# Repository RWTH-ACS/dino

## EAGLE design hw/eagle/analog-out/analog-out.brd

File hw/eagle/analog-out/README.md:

dino analog-out
Copyright (c) 2022 Manuel Pitz
Copyright (c) 2022 Niklas Eiling

This repository describes Open Hardware and is licensed under the CERN-OHL-W v2

You may redistribute and modify this documentation and make products
using it under the terms of the CERN-OHL-W v2 (https:/cern.ch/cern-ohl).
This documentation is distributed WITHOUT ANY EXPRESS OR IMPLIED
WARRANTY, INCLUDING OF MERCHANTABILITY, SATISFACTORY QUALITY
AND FITNESS FOR A PARTICULAR PURPOSE. Please see the CERN-OHL-W v2
for applicable conditions.

Source location: https://github.com/RWTH-ACS/dino

As per CERN-OHL-W v2 section 4.1, should You produce hardware based on
these sources, You must maintain the Source Location visible on the
external case of the White Rabbit switch or other product you make using
this documentation.

# dino - analog out

### DAC Module - LTC2642-16bit

### Isolator: ADUM210N

## Module Interface

## Architecture

## Components

| Tag               | Component      | Stock | Notes / Description |
|-------------------|----------------|-------|--------|
| DAC               | | 2     |        |
| DC/DC             | [TDN3-1221WISM](https://www.tracopower.com/sites/default/files/products/datasheets/tdn1wism_datasheet.pdf)  | 5     |        |
| I2C Isolator      | [ADUM1250/1251](https://www.analog.com/media/en/technical-documentation/data-sheets/ADUM1250_1251.pdf)  | 1     |        |
| CONV Isolator     | [ADUM4120](https://www.analog.com/media/en/technical-documentation/data-sheets/ADuM4120-4120-1.pdf)       | 2     |        |
| CLK Isolator      | [ADM2486](https://www.analog.com/media/en/technical-documentation/data-sheets/ADM2486.pdf)       | 2     |        |
| Shift Register    | [TCA9534](https://www.ti.com/lit/ds/symlink/tca9534.pdf?ts=1607878079799&ref_url=https%253A%252F%252Fwww.ti.com%252Fproduct%252FTCA9534%253Futm_source%253Dgoogle%2526utm_medium%253Dcpc%2526utm_campaign%253Dasc-null-null-gpn_en-cpc-pf-google-wwe%2526utm_content%253Dtca9534%2526ds_k%253DTCA9534%2526dcm%253Dyes%2526gclid%253DCjwKCAiAlNf-BRB_EiwA2osbxSn2BJCqIPv8pv_chYE8HBU01zoYS7veeZFo8f20QknqdfCq58b9ORoCjIIQAvD_BwE%2526gclsrc%253Daw.ds)        | 0     |        |
| Instrumentation Amplifier  | [AD8250](https://www.analog.com/media/en/technical-documentation/data-sheets/AD8250.pdf)        | 0     |        |
| Analog Switch     | [MAX4564](https://datasheets.maximintegrated.com/en/ds/MAX4564.pdf)        |       |        |
| Voltage Reference | [LT6654](https://www.analog.com/media/en/technical-documentation/data-sheets/6654fh.pdf)         | 0     |        |
| ROHM              | [BR24T1MF-3AME2](https://fscdn.rohm.com/en/products/databook/datasheet/ic/memory/eeprom/br24t1m-3am-e.pdf) | 0     |        |
| RJ45 Connector    | -              |       |        |
|FUSE|           |       |        |
|Double D flip flop|[74HC74](https://docs.rs-online.com/0bd3/0900766b81620dd2.pdf)|0|[digi-key](https://www.digikey.de/product-detail/en/nexperia-usa-inc/74HC74D-653/1727-2824-2-ND/763094)|
|OR gate IC|[SN74LVC1G32](https://www.ti.com/lit/ds/symlink/sn74lvc1g32.pdf?ts=1616658660326&ref_url=https%253A%252F%252Fwww.google.com%252F)|0|no info about freq. [digi-key](https://www.digikey.de/product-detail/en/texas-instruments/SN74LVC1G32DCKR/296-9848-2-ND/381315)|
|AND gate IC|[SN74LVC1G08-Q1](https://www.ti.com/lit/ds/symlink/sn74lvc1g08-q1.pdf?ts=1616684039458&ref_url=https%253A%252F%252Fwww.google.com%252F)|0|no info about freq. [diig-key](https://www.digikey.de/product-detail/en/texas-instruments/SN74LVC1G08QDBVRQ1/296-24187-2-ND/1591986)|

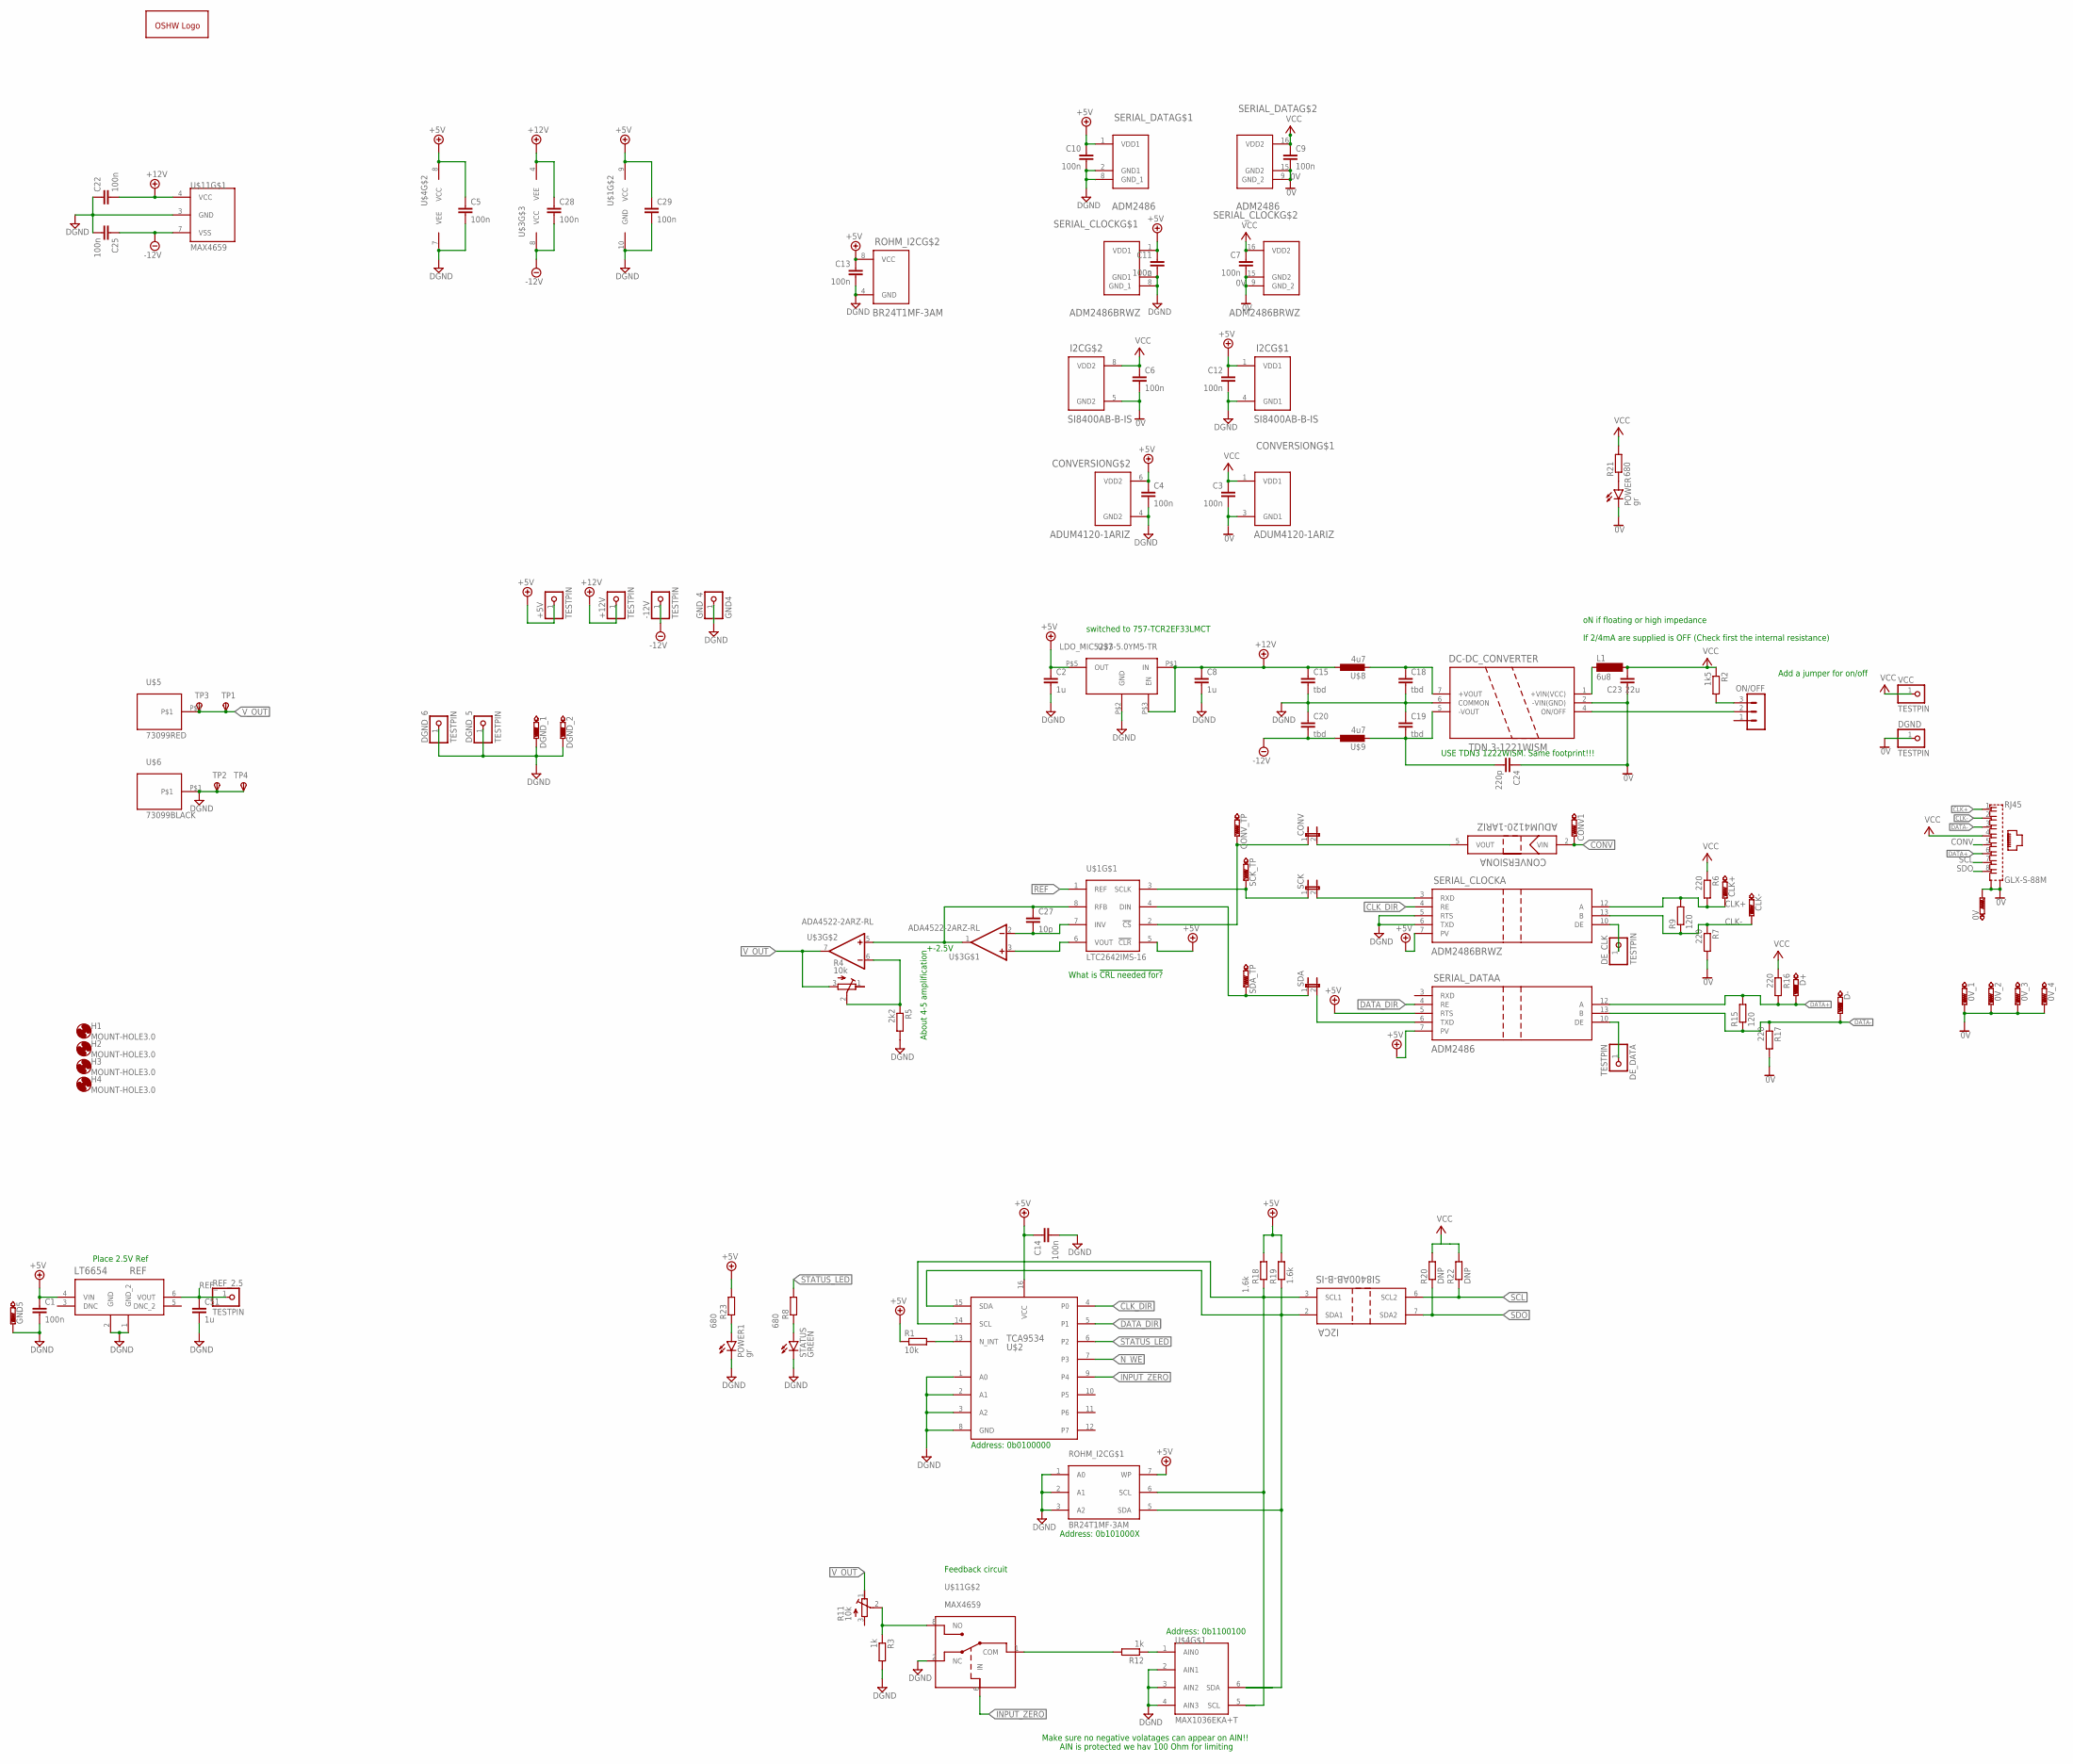
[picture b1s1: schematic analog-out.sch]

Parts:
0V, 0V_1, 0V_2, 0V_3, 0V_4: PTR1B1,27; B1,27
+5V, +12V: TESTPIN; 1X01
-12V: TESTPIN; 1X01
C1, C5, C22, C25, C28, C29: 100n; C0805; DIGIKEY 478-7962-1-ND
C2, C8: 1u; C0805K; DIGIKEY 478-7962-1-ND
C3, C4, C6, C7, C9, C10, C11, C12, C13, C14: 100n; C0805K; DIGIKEY 478-7962-1-ND
C15, C18, C19, C20: tbd; C0805K; DIGIKEY 478-7962-1-ND
C23: 22u; C1206; DIGIKEY 399-17625-1-ND
C24: 220p; C1808; DIGIKEY 478-10448-2-ND
C27: 10p; C0805; DIGIKEY 478-7962-1-ND
C51: 1u; C0805; DIGIKEY 1276-6471-1-ND
CLK+: PTR1B1,27; B1,27
CLK-: PTR1B1,27; B1,27
CONV: JP1E; JP1
CONV1: PTR1B1,27; B1,27
CONVERSION: ADUM4120-1ARIZ; RI_6_1_ADI; DIGIKEY ADUM4120-1ARIZ-ND
CONV_TP: PTR1B1,27; B1,27
D+: PTR1B1,27; B1,27
D-: PTR1B1,27; B1,27
DC-DC_CONVERTER: TDN 3-1221WISM; TDN3_TRP; DIGIKEY TDN3-1222WISM-ND
DE_CLK: TESTPIN; 1X01
DE_DATA: TESTPIN; 1X01
DGND: TESTPIN; 1X01
DGND_1, DGND_2: PTR1B1,27; B1,27
DGND_5, DGND_6: TESTPIN; 1X01
GND5: PTR1B1,27; B1,27
GND_4: GND4; 1X01
GOLD_ORB_SM1: OSHWLOGOLOGO8MM; OSHW_8MM
H1, H2, H3, H4: MOUNT-HOLE3.0; 3,0
I2C: SI8400AB-B-IS; R_8_ADI; MOUSER 634-SI8400AB-B-IS
L1: 6u8; SM-NE29; DIGIKEY 1951-1045-ND
ON/OFF: MA03-1; DIGIKEY 732-5316-ND
POWER, POWER1: gr; SML0805; DIGIKEY LTST-C170GKT
R1: 10k; R0805; DIGIKEY P10KDATR-ND
R2: 1k5; R0805; DIGIKEY P1.5KDATR-ND
R3: 1k; R0805; DIGIKEY Y1629-120DTR-ND
R4, R11: 10k; RTRIMT93YA
R5: 2k2; R0805; DIGIKEY Y1629-120DTR-ND
R6, R7, R16, R17: 220; R0805; DIGIKEY Y1624195R000Q9R-ND
R8, R23: 680; R0805
R9, R15: 120; R0805; DIGIKEY Y1629-120DTR-ND
R12: 1k; R0805
R18, R19: 1.6k; R0805
R20, R22: DNP; R0805
R21: 680; R0805; DIGIKEY A129747TR-ND
REF: LT6654; S_6_ADI; DIGIKEY 505-LT6654AIS6-2.5#TRMPBFTR-ND
REF_2.5: TESTPIN; 1X01
RJ45: GLX-S-88M; DIGIKEY 2092-GLX-S-88M-ND
ROHM_I2C: BR24T1MF-3AM; BR24T1MFJ-3AM; DIGIKEY BR24T1MF-3AME2TR-ND
SCK: JP1E; JP1
SCK_TP: PTR1B1,27; B1,27
SDA: JP1E; JP1
SDA_TP: PTR1B1,27; B1,27
SERIAL_CLOCK: ADM2486BRWZ; RW_16_ADI; DIGIKEY ADM2486BRWZ-REELTR-ND
SERIAL_DATA: ADM2486; RW_16_ADI; DIGIKEY ADM2486BRWZ-REELTR-ND
STATUS: GREEN; CHIPLED_0805; DIGIKEY LTST-C170GKT
TP1, TP2, TP3, TP4: TPSTP20SQ; TP20SQ
U$1: LTC2642IMS-16; MSOP10
U$2: TCA9534; TSSOP16L; DIGIKEY 296-40574-2-ND
U$3: ADA4522-2ARZ-RL; MSOP8
U$4: MAX1036EKA+T; SOT23-8L
U$5: 73099RED; 4MM_BANANA
U$6: 73099BLACK; 4MM_BANANA
U$7: LDO_MIC5233-5.0YM5-TR; SOT23-5
U$8, U$9: 4u7; L5038P
U$11: MAX4659; UMAX8; MOUSER 700-MAX4659EUA
VCC: TESTPIN; 1X01

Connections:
0V: 0V.TP, 0V_1.TP, 0V_2.TP, 0V_3.TP, 0V_4.TP, C3.2, C6.2, C7.2, C9.2, C23.1, C24.1, CONVERSION.3 (GND1), DC-DC_CONVERTER.2 (-VIN(GND)), DGND.1, I2C.5 (GND2), POWER.C, R7.2, R17.2, RJ45.S1, RJ45.S2, SERIAL_CLOCK.9 (GND_2), SERIAL_CLOCK.15 (GND2), SERIAL_DATA.9 (GND_2), SERIAL_DATA.15 (GND2)
+5V: +5V.1, C1.1, C2.1, C4.1, C5.1, C10.1, C11.1, C12.1, C13.1, C14.1, C29.1, CONVERSION.6 (VDD2), I2C.1 (VDD1), R1.1, R18.2, R19.2, R23.2, REF.4 (VIN), ROHM_I2C.7 (WP), ROHM_I2C.8 (VCC), SERIAL_CLOCK.1 (VDD1), SERIAL_CLOCK.7 (PV), SERIAL_DATA.1 (VDD1), SERIAL_DATA.5 (RTS), SERIAL_DATA.7 (PV), U$1.5 (!CLR), U$1.9 (VCC), U$2.16 (VCC), U$4.8 (VCC), U$7.P$5 (OUT)
+12V: +12V.1, C8.1, C15.1, C22.2, C28.1, U$3.4 (VEE), U$7.P$1 (IN), U$7.P$3 (EN), U$8.1, U$11.4 (VCC)
-12V: -12V.1, C20.2, C25.1, C28.2, U$3.8 (VCC), U$9.1, U$11.7 (VSS)
CLK+: CLK+.TP, R6.2, R9.2, RJ45.1, SERIAL_CLOCK.12 (A)
CLK-: CLK-.TP, R7.1, R9.1, RJ45.2, SERIAL_CLOCK.13 (B)
CLK_DIR: SERIAL_CLOCK.4 (RE), U$2.4 (P0)
CONV: CONV1.TP, CONVERSION.2 (VIN), RJ45.5
CONV_ADC: CONV.1, CONV_TP.TP, U$1.2 (!CS)
DATA+: D+.TP, R15.2, R16.2, RJ45.6, SERIAL_DATA.12 (A)
DATA-: D-.TP, R15.1, R17.1, RJ45.3, SERIAL_DATA.13 (B)
DATA_DIR: SERIAL_DATA.4 (RE), U$2.5 (P1)
DGND: C1.2, C2.2, C4.2, C5.2, C8.2, C10.2, C11.2, C12.2, C13.2, C14.2, C15.2, C18.2, C19.1, C20.1, C22.1, C25.2, C29.2, C51.2, CONVERSION.4 (GND2), DC-DC_CONVERTER.6 (COMMON), DGND_1.TP, DGND_2.TP, DGND_5.1, DGND_6.1, GND5.TP, GND_4.1, I2C.4 (GND1), POWER1.C, R3.2, R5.2, REF.1 (GND_2), REF.2 (GND), ROHM_I2C.1 (A0), ROHM_I2C.2 (A1), ROHM_I2C.3 (A2), ROHM_I2C.4 (GND), SERIAL_CLOCK.2 (GND1), SERIAL_CLOCK.5 (RTS), SERIAL_CLOCK.6 (TXD), SERIAL_CLOCK.8 (GND_1), SERIAL_DATA.2 (GND1), SERIAL_DATA.8 (GND_1), STATUS.C, TP2.TP, TP4.TP, U$1.10 (GND), U$2.1 (A0), U$2.2 (A1), U$2.3 (A2), U$2.8 (GND), U$4.2 (AIN1), U$4.3 (AIN2), U$4.4 (AIN3), U$4.7 (VEE), U$6.P$1, U$7.P$2 (GND), U$11.2 (NC), U$11.3 (GND)
INPUT_ZERO: U$2.9 (P4), U$11.6 (IN)
unnamed: C27.2, U$1.7 (INV), U$3.2 (-IN)
unnamed: R1.2, U$2.13 (N_INT)
unnamed: DE_CLK.1, SERIAL_CLOCK.10 (DE)
unnamed: SDA.2, SERIAL_DATA.6 (TXD)
unnamed: U$1.6 (VOUT), U$3.3 (+IN)
unnamed: C19.2, C24.2, DC-DC_CONVERTER.5 (-VOUT), U$9.2
unnamed: DE_DATA.1, SERIAL_DATA.10 (DE)
unnamed: C27.1, U$1.8 (RFB), U$3.1 (OUT), U$3.5 (+IN)
unnamed: DC-DC_CONVERTER.1 (+VIN(VCC)), L1.1
unnamed: ON/OFF.3, R2.2
unnamed: DC-DC_CONVERTER.4 (ON/OFF), ON/OFF.2
unnamed: R12.1, U$4.1 (AIN0)
unnamed: I2C.2 (SDA1), R19.1, ROHM_I2C.5 (SDA), U$2.15 (SDA), U$4.6 (SDA)
unnamed: R4.2 (S), R5.1, U$3.6 (-IN)
unnamed: R3.1, R11.2 (S), U$11.8 (NO)
unnamed: I2C.3 (SCL1), R18.1, ROHM_I2C.6 (SCL), U$2.14 (SCL), U$4.5 (SCL)
unnamed: R12.2, U$11.1 (COM)
unnamed: C18.1, DC-DC_CONVERTER.7 (+VOUT), U$8.2
unnamed: R8.1, STATUS.A
unnamed: CONV.2, CONVERSION.5 (VOUT)
unnamed: SCK.1, SCK_TP.TP, U$1.3 (SCLK)
unnamed: POWER1.A, R23.1
unnamed: POWER.A, R21.1
N_WE: U$2.7 (P3)
REF_: C51.1, REF.6 (VOUT), REF_2.5.1, U$1.1 (REF)
SCK_ADC: SCK.2, SERIAL_CLOCK.3 (RXD)
SCL: I2C.6 (SCL2), R22.1, RJ45.7
SDO: I2C.7 (SDA2), R20.1, RJ45.8
SDO_ADC: SDA.1, SDA_TP.TP, U$1.4 (DIN)
STATUS_LED: R8.2, U$2.6 (P2)
V+: C3.1, C6.1, C7.1, C9.1, C23.2, CONVERSION.1 (VDD1), I2C.8 (VDD2), L1.2, R2.1, R6.1, R16.1, R20.2, R21.2, R22.2, RJ45.4, SERIAL_CLOCK.16 (VDD2), SERIAL_DATA.16 (VDD2), VCC.1
V_OUT: R4.3 (A), R11.1 (E), TP1.TP, TP3.TP, U$3.7 (OUT), U$5.P$1

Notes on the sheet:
oN if floating or high impedance
If 2/4mA are supplied is OFF (Check first the internal resistance)
Add a jumper for on/off
What is !CRL needed for?
Make sure no negative volatages can appear on AIN!!
Feedback circuit
Address: 0b1100100
Address: 0b101000X
Address: 0b0100000
USE TDN3 1222WISM. Same footprint!!!
About 4-5 amplification
AIN is protected we hav 100 Ohm for limiting
+-2.5V
switched to 757-TCR2EF33LMCT
Place 2.5V Ref

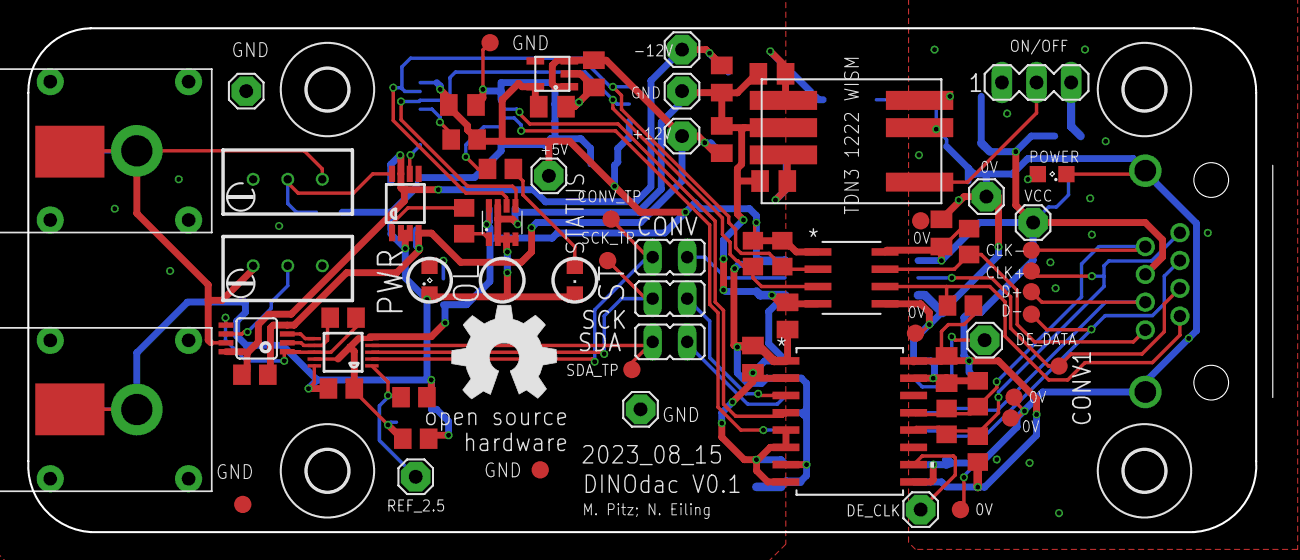
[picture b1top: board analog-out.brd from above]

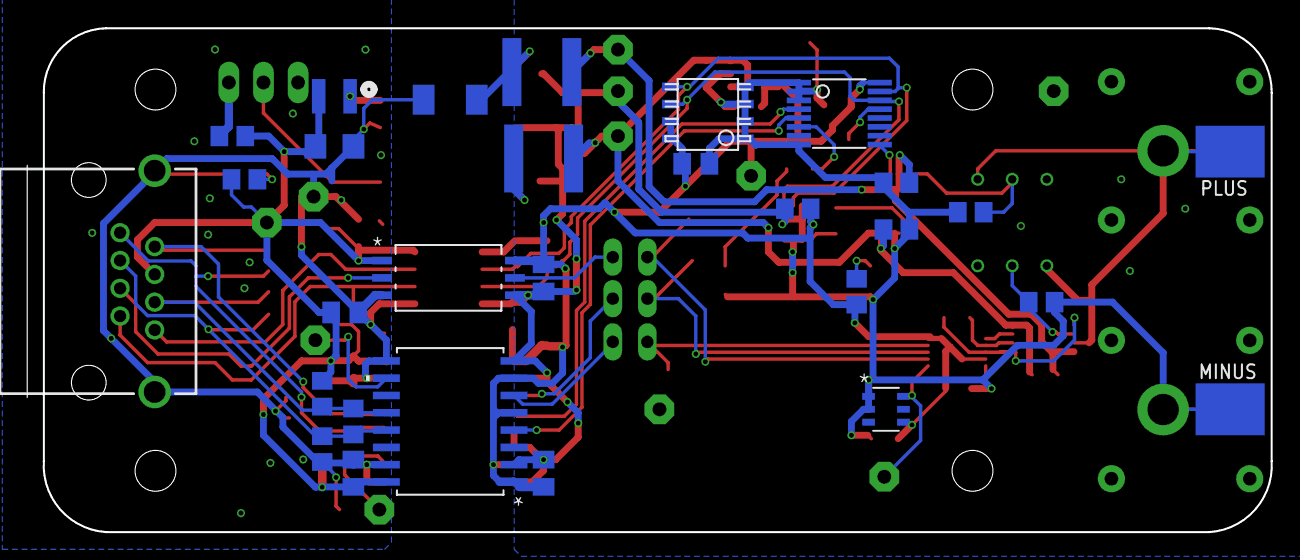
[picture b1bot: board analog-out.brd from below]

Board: 2 copper layers, 91.4 x 37.0 mm, 108 parts (28 on the bottom side), 45 nets.

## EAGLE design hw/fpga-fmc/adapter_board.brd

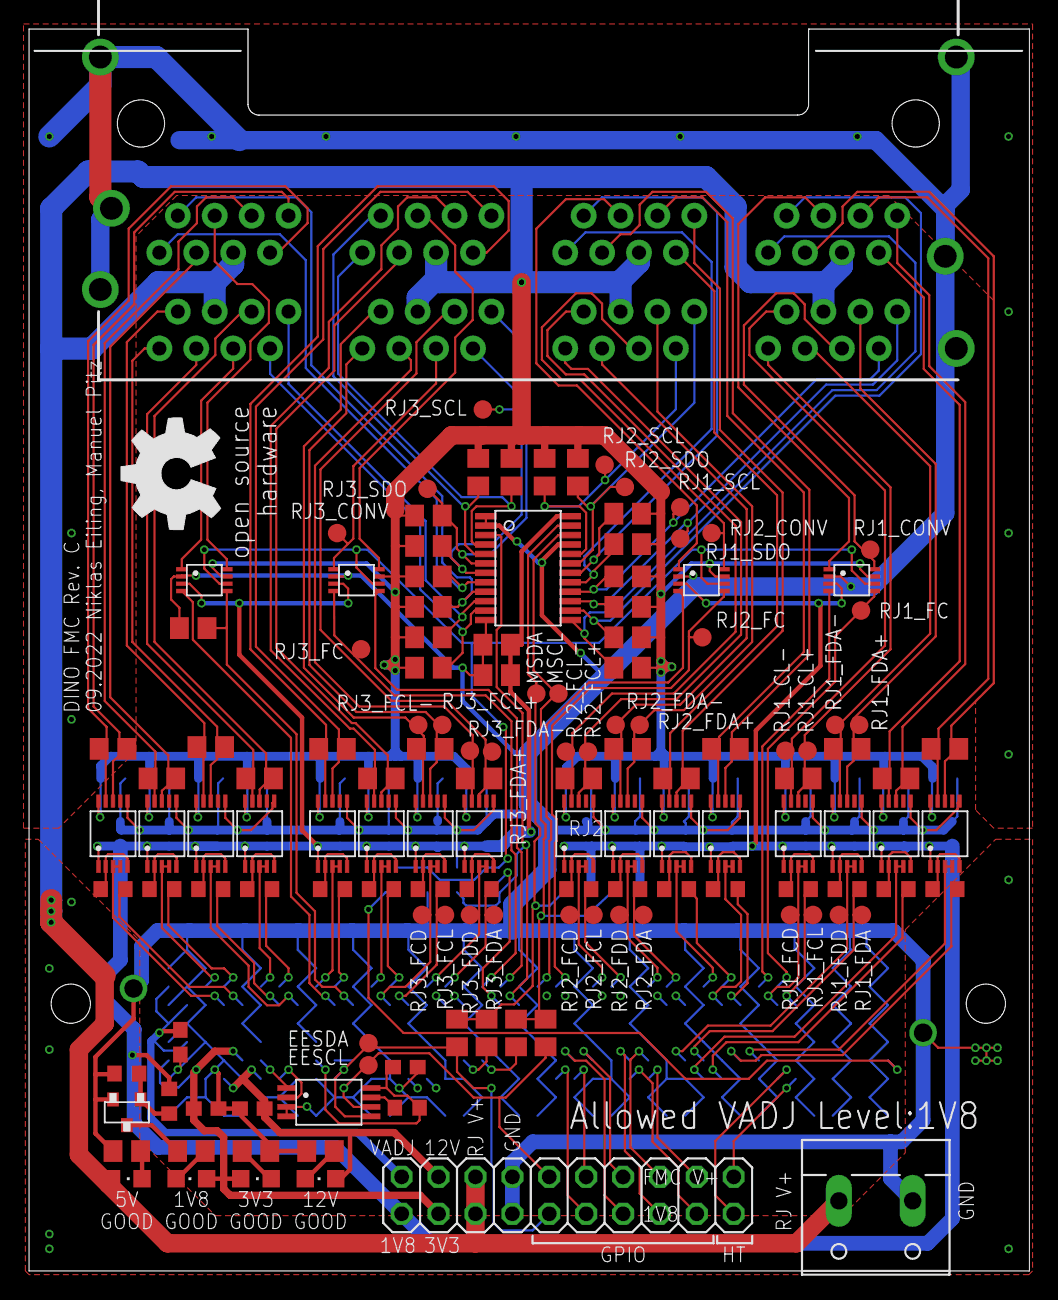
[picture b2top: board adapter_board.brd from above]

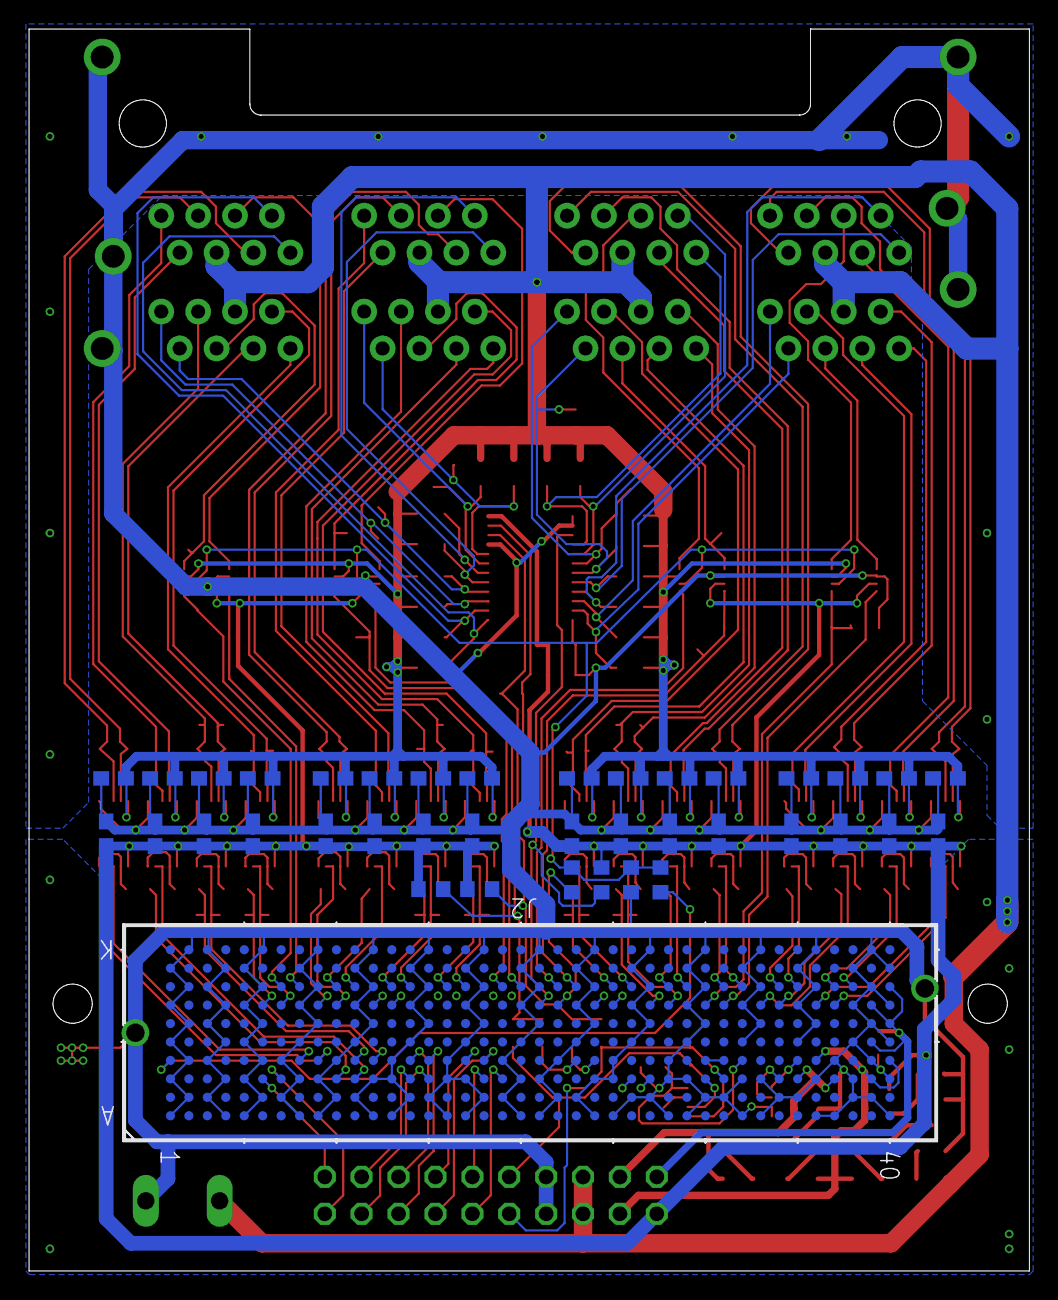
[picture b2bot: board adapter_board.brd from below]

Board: 2 copper layers, 68.9 x 85.5 mm, 176 parts (39 on the bottom side), 149 nets.

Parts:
1V8_GOOD, 3V3_GOOD, 5V_GOOD, 12V_GOOD: CHIPLED_0805
C1, C2, C5, C6, C7, C8, C9, C10, C11, C12, C13, C14, C15, C16, C17, C18, C19, C20, C21, C22, C23, C24, C25, C26, C27, C28, C29, C30, C31, C32, C33, C34, C35, C36, C37, C39: 100n; C0603
C3: 100n; C0805
C4: 1u; C0805
EESCL: TPB1,27; B1,27
EESDA: TPB1,27; B1,27
IC1: M24C02; TSSOP-8
J1: 5569262-1; TE_5569262-1
J2: ASP-134488-01; CONN_ASP-134488-01_SAI
JP1: 2X10
MSCL: TPB1,27; B1,27
MSDA: TPB1,27; B1,27
R1, R22, R24, R26, R28, R30, R32, R34, R36, R38, R40, R42, R44, R46, R48, R50: 120R; R0805
R2, R23, R25, R27, R29, R31, R33, R35, R37, R39, R41, R43, R45, R47, R49, R51: 100R; R0603
R3, R4, R8, R9, R10, R11, R12, R13, R14, R15, R16, R17, R18, R19, R20, R21: 4.7k; R0805
R5, R6: 4.7k; R0603
R7, R55, R61: 10k; R0603
R52: NB; R0603
R53: 330R; R0805
R54: 1k; R0805
R56, R62: 130R; R0805
R57: 0R DNP; R0603
R58: 0R; R0603
R59: DNP; R0805
R60: 10R; R0603
R63, R64: 0R DNP; R0805
R65, R66: 0R; R0805
RJ1_CL+, RJ1_CL-, RJ1_CONV, RJ1_FC, RJ1_FCD, RJ1_FCL, RJ1_FDA, RJ1_FDA+, RJ1_FDA-, RJ1_FDD, RJ1_SCL, RJ1_SDO, RJ2_CONV, RJ2_FC, RJ2_FCD, RJ2_FCL, RJ2_FCL+, RJ2_FCL-, RJ2_FDA, RJ2_FDA+, RJ2_FDA-, RJ2_FDD, RJ2_SCL, RJ2_SDO, RJ3_CONV, RJ3_FC, RJ3_FCD, RJ3_FCL, RJ3_FCL+, RJ3_FCL-, RJ3_FDA, RJ3_FDA+, RJ3_FDA-, RJ3_FDD, RJ3_SCL, RJ3_SDO: TPB1,27; B1,27
U1, U2, U3, U4, U5, U6, U7, U8, U9, U10, U11, U12, U13, U14, U15, U16: ADM3066E; MSOP-10
U17: TCA9548A; PCA9548
U18, U19, U20, U21: TXS0102; VSSOP-8
U40: IRLML2502; SOT23-IRLML
U$1: OSHW_8MM
X1: W237-132

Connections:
0V: C1.2, C2.2, C3.1, C4.1, C5.2, C6.2, C7.2, C8.2, C9.2, C10.2, C11.2, C12.2, C13.2, C14.2, C15.2, C16.2, C17.2, C18.2, C19.2, C20.2, C21.2, C22.2, C23.2, C24.2, C25.2, C26.2, C27.2, C28.2, C29.2, C30.2, C31.2, C32.2, C33.2, C34.2, C35.1, C36.1, C37.1, C39.1, IC1.3, IC1.4, J1.1, J1.2, J1.3, J1.4, J1.5, J1.6, J2.401, J2.402, J2.A1, J2.A4, J2.A5, J2.A8, J2.A9, J2.A12, J2.A13, J2.A16, J2.A17, J2.A20, J2.A21, J2.A24, J2.A25, J2.A28, J2.A29, J2.A32, J2.A33, J2.A36, J2.A37, J2.A40, J2.B2, J2.B3, J2.B6, J2.B7, J2.B10, J2.B11, J2.B14, J2.B15, J2.B18, J2.B19, J2.B22, J2.B23, J2.B26, J2.B27, J2.B30, J2.B31, J2.B34, J2.B35, J2.B38, J2.B39, J2.C1, J2.C4, J2.C5, J2.C8, J2.C9, J2.C12, J2.C13, J2.C16, J2.C17, J2.C20, J2.C21, J2.C24, J2.C25, J2.C28, J2.C29, J2.C32, J2.C33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
1V8: C1.1, C3.2, C4.2, C5.1, C7.1, C9.1, C11.1, C13.1, C15.1, C17.1, C19.1, C21.1, C23.1, C25.1, C27.1, C29.1, C31.1, C33.1, JP1.1, R5.2, R6.2, R7.2, R60.2, U1.P0, U2.P0, U3.P0, U4.P0, U5.P0, U6.P0, U7.P0, U8.P0, U9.P0, U10.P0, U11.P0, U12.P0, U13.P0, U14.P0, U15.P0, U16.P0, U17.P23, U18.3, U19.3, U20.3, U21.3
1V8_POWER_GOOD: J2.D1, R58.1
3P3VAUX: C39.2, IC1.8, J2.D32, R52.2
5V: 5V_GOOD.A, C2.1, C6.1, C8.1, C10.1, C12.1, C14.1, C16.1, C18.1, C20.1, C22.1, C24.1, C26.1, C28.1, C30.1, C32.1, C34.1, J1.1.4, J1.2.4, J1.3.4, J1.4.4, J1.5.5, J1.6.5, J1.7.5, J1.8.5, JP1.5, JP1.6, R3.2, R4.2, R8.2, R9.2, R10.2, R11.2, R12.2, R13.2, R14.2, R15.2, R16.2, R17.2, R18.2, R19.2, R20.2, R21.2, U1.P9, U2.P9, U3.P9, U4.P9, U5.P9, U6.P9, U7.P9, U8.P9, U9.P9, U10.P9, U11.P9, U12.P9, U13.P9, U14.P9, U15.P9, U16.P9, U18.7, U19.7, U20.7, U21.7, X1.2
+3V3: 1V8_GOOD.A, 3V3_GOOD.A, C36.2, J2.C39, J2.D36, J2.D38, J2.D40, JP1.3
+12V: 12V_GOOD.A, C37.2, J2.C35, J2.C37, JP1.4
CONV_OE: R55.2, R57.1, R58.2, U18.6, U19.6, U20.6, U21.6
FMC_DP0_M2C_N: J2.C7, JP1.19
FMC_DP0_M2C_P: J2.C6, JP1.20
FMC_IIC_SCL: EESCL.TP, IC1.6, J2.C30, JP1.10, R64.1
FMC_IIC_SDA: EESDA.TP, IC1.5, J2.C31, JP1.9, R63.1
FMC_LA00_CC_N: J2.G7, RJ1_FCD.TP, U13.P2, U13.P3
FMC_LA00_CC_P: J2.G6, R45.2, RJ1_FCL.TP
FMC_LA01_CC_N: J2.D9, R51.2
FMC_LA01_CC_P: J2.D8, U16.P2, U16.P3
FMC_LA02_N: J2.H8, U21.4
FMC_LA02_P: J2.H7, RJ1_FC.TP, U21.5
FMC_LA03_N: J2.G10, U12.P2, U12.P3
FMC_LA03_P: J2.G9, R43.2
FMC_LA04_N: J2.H11, U11.P2, U11.P3
FMC_LA04_P: J2.H10, R41.2
FMC_LA05_N: J2.D12, RJ1_FDD.TP, U14.P2, U14.P3
FMC_LA05_P: J2.D11, R47.2, RJ1_FDA.TP
FMC_LA06_N: J2.C11, U15.P2, U15.P3
FMC_LA06_P: J2.C10, R49.2
FMC_LA07_N: J2.H14, RJ2_FDD.TP, U10.P2, U10.P3
FMC_LA07_P: J2.H13, R39.2, RJ2_FDA.TP
FMC_LA09_N: J2.D15, JP1.15
FMC_LA09_P: J2.D14, JP1.16
FMC_LA10_N: J2.C15, JP1.17
FMC_LA10_P: J2.C14, JP1.18
FMC_LA11_N: J2.H17, RJ2_FCD.TP, U9.P2, U9.P3
FMC_LA11_P: J2.H16, R37.2, RJ2_FCL.TP
FMC_LA13_N: J2.D18, JP1.13
FMC_LA13_P: J2.D17, JP1.14
FMC_LA14_N: J2.C19, JP1.11
FMC_LA14_P: J2.C18, JP1.12
FMC_LA15_N: J2.H20, U20.4
FMC_LA15_P: J2.H19, RJ2_FC.TP, U20.5
FMC_LA19_N: J2.H23, RJ3_FC.TP, U19.4
FMC_LA19_P: J2.H22, U19.5
FMC_LA20_N: J2.G22, R57.2
FMC_LA20_P: J2.G21, R7.1, U17.P2
FMC_LA21_N: J2.H26, RJ3_FDD.TP, U8.P2, U8.P3
FMC_LA21_P: J2.H25, R35.2, RJ3_FDA.TP
FMC_LA23_N: J2.D24, R65.2
FMC_LA23_P: J2.D23, R66.2
FMC_LA24_N: J2.H29, U6.P2, U6.P3
FMC_LA24_P: J2.H28, R31.2
FMC_LA25_N: J2.G28, RJ3_FCD.TP, U7.P2, U7.P3
FMC_LA25_P: J2.G27, R33.2, RJ3_FCL.TP
FMC_LA28_N: J2.H32, U5.P2, U5.P3
FMC_LA28_P: J2.H31, R29.2
FMC_LA29_N: J2.G31, U18.4
FMC_LA29_P: J2.G30, R59.1, U18.5
FMC_LA30_N: J2.H35, U4.P2, U4.P3
FMC_LA30_P: J2.H34, R27.2
FMC_LA31_N: J2.G34, R25.2
FMC_LA31_P: J2.G33, U3.P2, U3.P3
FMC_LA32_N: J2.H38, U2.P2, U2.P3
FMC_LA32_P: J2.H37, R23.2
FMC_LA33_N: J2.G37, U1.P2, U1.P3
FMC_LA33_P: J2.G36, R2.2
FMC_TDI_TDO: J2.D30, J2.D31
GA0: IC1.2, J2.C34
GA1: IC1.1, J2.D35
I2C_SCL: MSCL.TP, R6.1, R64.2, R66.1, U17.P21
I2C_SDA: MSDA.TP, R5.1, R63.2, R65.1, U17.P22
LSIO1: R2.1, U1.P1, U1.P4
LSIO2: R23.1, U2.P1, U2.P4
LSIO3: R25.1, U3.P1, U3.P4
LSIO4: R27.1, U4.P1, U4.P4
LSIO5: R29.1, U5.P1, U5.P4
LSIO6: R31.1, U6.P1, U6.P4
LSIO7: R33.1, U7.P1, U7.P4
LSIO8: R35.1, U8.P1, U8.P4
LSIO9: R37.1, U9.P1, U9.P4
LSIO10: R39.1, U10.P1, U10.P4
LSIO11: R41.1, U11.P1, U11.P4
LSIO12: R43.1, U12.P1, U12.P4
LSIO13: R45.1, U13.P1, U13.P4
LSIO14: R47.1, U14.P1, U14.P4
LSIO15: R49.1, U15.P1, U15.P4
LSIO16: R51.1, U16.P1, U16.P4
unnamed: IC1.7, R52.1
unnamed: 12V_GOOD.C, R54.2
unnamed: 3V3_GOOD.C, R56.2
unnamed: 5V_GOOD.C, R53.2
unnamed: R60.1, R61.1, U40.P1
unnamed: R62.2, U40.P3
unnamed: 1V8_GOOD.C, R62.1
RJ1_CLK_N: J1.1.2, R44.2, RJ1_CL-.TP, U13.P8
RJ1_CLK_P: J1.1.1, R44.1, RJ1_CL+.TP, U13.P7
RJ1_CONV: J1.1.5, RJ1_CONV.TP, U21.8
RJ1_DATA_N: J1.1.3, R46.2, RJ1_FDA-.TP, U14.P8
RJ1_DATA_P: J1.1.6, R46.1, RJ1_FDA+.TP, U14.P7
RJ1_SCL: J1.1.7, R17.1, RJ1_SCL.TP, U17.P15
RJ1_SDO: J1.1.8, R16.1, RJ1_SDO.TP, U17.P14
RJ2_CLK_N: J1.2.2, R36.2, RJ2_FCL-.TP, U9.P8
RJ2_CLK_P: J1.2.1, R36.1, RJ2_FCL+.TP, U9.P7
RJ2_CONV: J1.2.5, RJ2_CONV.TP, U20.8
RJ2_DATA_N: J1.2.3, R38.2, RJ2_FDA-.TP, U10.P8
RJ2_DATA_P: J1.2.6, R38.1, RJ2_FDA+.TP, U10.P7
RJ2_SCL: J1.2.7, R21.1, RJ2_SCL.TP, U17.P19
RJ2_SDO: J1.2.8, R20.1, RJ2_SDO.TP, U17.P18
RJ3_CLK_N: J1.3.2, R32.2, RJ3_FCL-.TP, U7.P8
RJ3_CLK_P: J1.3.1, R32.1, RJ3_FCL+.TP, U7.P7
RJ3_CONV: J1.3.5, RJ3_CONV.TP, U19.1
RJ3_DATA_N: J1.3.3, R34.2, RJ3_FDA-.TP, U8.P8
RJ3_DATA_P: J1.3.6, R34.1, RJ3_FDA+.TP, U8.P7
RJ3_SCL: J1.3.7, R9.1, RJ3_SCL.TP, U17.P6
RJ3_SDO: J1.3.8, R8.1, RJ3_SDO.TP, U17.P5
RJ4_CLK_N: J1.4.2, R24.2, U3.P8
RJ4_CLK_P: J1.4.1, R24.1, U3.P7
RJ4_CONV: J1.4.5, U18.1
RJ4_DATA_N: J1.4.3, R26.2, U4.P8
RJ4_DATA_P: J1.4.6, R26.1, U4.P7
RJ4_SCL: J1.4.7, R13.1, U17.P10
RJ4_SDO: J1.4.8, R12.1, U17.P9
RJ5_CLK_N: J1.5.7, R48.2, U15.P8
RJ5_CLK_P: J1.5.8, R48.1, U15.P7
RJ5_CONV: J1.5.4, U21.1
RJ5_DATA_N: J1.5.6, R50.2, U16.P8
RJ5_DATA_P: J1.5.3, R50.1, U16.P7
RJ5_SCL: J1.5.2, R15.1, U17.P13
RJ5_SDO: J1.5.1, R14.1, U17.P12
RJ6_CLK_N: J1.6.7, R40.2, U11.P8
RJ6_CLK_P: J1.6.8, R40.1, U11.P7
RJ6_CONV: J1.6.4, U20.1
RJ6_DATA_N: J1.6.6, R42.2, U12.P8
RJ6_DATA_P: J1.6.3, R42.1, U12.P7
RJ6_SCL: J1.6.2, R19.1, U17.P17
RJ6_SDO: J1.6.1, R18.1, U17.P16
RJ7_CLK_N: J1.7.7, R28.2, U5.P8
RJ7_CLK_P: J1.7.8, R28.1, U5.P7
RJ7_CONV: J1.7.4, U19.8
RJ7_DATA_N: J1.7.6, R30.2, U6.P8
RJ7_DATA_P: J1.7.3, R30.1, U6.P7
RJ7_SCL: J1.7.2, R4.1, U17.P4
RJ7_SDO: J1.7.1, R3.1, U17.P3
RJ8_CLK_N: J1.8.7, R1.2, U1.P8
RJ8_CLK_P: J1.8.8, R1.1, U1.P7
RJ8_CONV: J1.8.4, U18.8
RJ8_DATA_N: J1.8.6, R22.2, U2.P8
RJ8_DATA_P: J1.8.3, R22.1, U2.P7
RJ8_SCL: J1.8.2, R11.1, U17.P8
RJ8_SDO: J1.8.1, R10.1, U17.P7
V+: C35.2, J2.E39, J2.F40, J2.G39, J2.H40, JP1.2

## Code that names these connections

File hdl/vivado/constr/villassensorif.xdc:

# Create 3Mhz derived clock
#create_generated_clock -name villassensorif_clk -source [get_pins bd_main_i/user_si570_sysclk_clk_p] -divide_by 4 [get_pins bd_main_i/c_counter_binary_0/THRESH0]


# CONV L/S activate
# Pull all CONV_OE to high to activate L/S outputs  (HPC0 | HPC1)
#   CONV_OE      <-> FMC_LA02_N    <-> K20 | K23
set_property PACKAGE_PIN K23 [get_ports conv_oe]
set_property IOSTANDARD LVCMOS18 [get_ports conv_oe]

# RJ1 interface (HPC0 | HPC1)
#    RJ1_CLK     <-> FMC_LA16_N  <-> C17 | C19
#    RJ1_CLK_DE  <-> FMC_LA16_P  <-> D17 | C18
#    RJ1_DATA    <-> FMC_LA15_N  <-> C16 | A19
#    RJ1_DATA_DE <-> FMC_LA15_P  <-> D16 | A18
#    RJ1_CONV    <-> FMC_LA12_N  <-> F18 | D19
#    RJ1_SCL     <-> SC5         <-> FMC_LA05_N
#    RJ1_SDO     <-> SD5         <-> FMC_LA05_P
set_property PACKAGE_PIN C19        [get_ports serial_clk_1]
set_property IOSTANDARD LVCMOS18    [get_ports serial_clk_1]
set_property PACKAGE_PIN C18        [get_ports {serial_clk_de[0]}]
set_property IOSTANDARD LVCMOS18    [get_ports {serial_clk_de[0]}]
set_property PACKAGE_PIN A19        [get_ports serial_data_1]
set_property IOSTANDARD LVCMOS18    [get_ports serial_data_1]
set_property PACKAGE_PIN A18        [get_ports {serial_data_de[0]}]
set_property IOSTANDARD LVCMOS18    [get_ports {serial_data_de[0]}]
set_property PACKAGE_PIN D19        [get_ports conv_1]
set_property IOSTANDARD LVCMOS18    [get_ports conv_1]


# RJ2 interface (HPC0 | HPC1)
#    RJ2_CLK     <-> FMC_LA10_N  <-> K15 | E22
#    RJ2_CLK_DE  <-> FMC_LA10_P  <-> L15 | F22
#    RJ2_DATA    <-> FMC_LA09_N  <-> G16 | F20
#    RJ2_DATA_DE <-> FMC_LA09_P  <-> H16 | G20
#    RJ2_CONV    <-> FMC_LA08_N  <-> E17 | H26
#    RJ2_SCL     <-> SC7         <-> FMC_LA05_N
#    RJ2_SDO     <-> SD7         <-> FMC_LA05_P
set_property PACKAGE_PIN E22        [get_ports serial_clk_2]
set_property IOSTANDARD LVCMOS18    [get_ports serial_clk_2]
set_property PACKAGE_PIN F22        [get_ports {serial_clk_de[1]}]
set_property IOSTANDARD LVCMOS18    [get_ports {serial_clk_de[1]}]
set_property PACKAGE_PIN F20        [get_ports serial_data_2]
set_property IOSTANDARD LVCMOS18    [get_ports serial_data_2]
set_property PACKAGE_PIN G20        [get_ports {serial_data_de[1]}]
set_property IOSTANDARD LVCMOS18    [get_ports {serial_data_de[1]}]
set_property PACKAGE_PIN H26        [get_ports conv_2]
set_property IOSTANDARD LVCMOS18    [get_ports conv_2]

# RJ3 interface (HPC0 | HPC1)
#    RJ3_CLK     <-> FMC_LA06_N    <-> G19 | H22
#    RJ3_CLK_DE  <-> FMC_LA06_P    <-> H19 | H21
#    RJ3_DATA    <-> FMC_LA01_CC_N <-> H17 | D24
#    RJ3_DATA_DE <-> FMC_LA01_CC_P <-> H18 | E24
#    RJ3_CONV    <-> FMC_LA03_P    <-> K19 | J21
#    RJ3_SCL     <-> SC1           <-> FMC_LA05_N
#    RJ3_SDO     <-> SD1           <-> FMC_LA05_P
set_property PACKAGE_PIN H22        [get_ports serial_clk_3]
set_property IOSTANDARD LVCMOS18    [get_ports serial_clk_3]
set_property PACKAGE_PIN H21        [get_ports {serial_clk_de[2]}]
set_property IOSTANDARD LVCMOS18    [get_ports {serial_clk_de[2]}]
set_property PACKAGE_PIN D24        [get_ports serial_data_3]
set_property IOSTANDARD LVCMOS18    [get_ports serial_data_3]
set_property PACKAGE_PIN E24        [get_ports {serial_data_de[2]}]
set_property IOSTANDARD LVCMOS18    [get_ports {serial_data_de[2]}]
set_property PACKAGE_PIN J21        [get_ports conv_3]
set_property IOSTANDARD LVCMOS18    [get_ports conv_3]

# RJ4 interface (HPC0 | HPC1)
#    RJ4_CLK     <-> FMC_DP0_C2M_N <-> R5  | AJ5
#    RJ4_CLK_DE  <-> FMC_DP0_C2M_P <-> R6  | AJ6
#    RJ4_DATA    <-> FMC_LA00_CC_N <-> F16 | B19
#    RJ4_DATA_DE <-> FMC_LA00_CC_P <-> F17 | B18
#    RJ4_CONV    <-> FMC_LA02_P    <-> L20 | K22
#    RJ4_SCL     <-> SC3           <-> FMC_LA05_N
#    RJ4_SDO     <-> SD3           <-> FMC_LA05_P
set_property PACKAGE_PIN K22        [get_ports {serial_clk_de[3]}]
set_property IOSTANDARD LVCMOS18    [get_ports {serial_clk_de[3]}]
set_property PACKAGE_PIN B18        [get_ports {serial_data_de[3]}]
set_property IOSTANDARD LVCMOS18    [get_ports {serial_data_de[3]}]
# RJ5 interface (HPC0 | HPC1)
#    RJ5_CLK     <-> FMC_LA11_N    <-> A12 | A21
#    RJ5_CLK_DE  <-> FMC_LA11_P    <-> A13 | A20
#    RJ5_DATA    <-> FMC_LA07_N    <-> J15 | C23
#    RJ5_DATA_DE <-> FMC_LA07_P    <-> J16 | D22
#    RJ5_CONV    <-> FMC_LA12_P    <-> G18 | E19
#    RJ5_SCL     <-> SC4           <-> FMC_LA05_N
#    RJ5_SDO     <-> SD4           <-> FMC_LA05_P
set_property PACKAGE_PIN A21        [get_ports serial_clk_5]
set_property IOSTANDARD LVCMOS18    [get_ports serial_clk_5]
set_property PACKAGE_PIN A20        [get_ports {serial_clk_de[4]}]
set_property IOSTANDARD LVCMOS18    [get_ports {serial_clk_de[4]}]
set_property PACKAGE_PIN C23        [get_ports serial_data_5]
set_property IOSTANDARD LVCMOS18    [get_ports serial_data_5]
set_property PACKAGE_PIN D22        [get_ports {serial_data_de[4]}]
set_property IOSTANDARD LVCMOS18    [get_ports {serial_data_de[4]}]
set_property PACKAGE_PIN E19        [get_ports conv_5]
set_property IOSTANDARD LVCMOS18    [get_ports conv_5]

# RJ6 interface (HPC0 | HPC1)
#    RJ6_CLK     <-> FMC_LA14_N    <-> C12 | D21
#    RJ6_CLK_DE  <-> FMC_LA14_P    <-> C13 | D20
#    RJ6_DATA    <-> FMC_LA13_N    <-> F15 | C22
#    RJ6_DATA_DE <-> FMC_LA13_P    <-> G15 | C21
#    RJ6_CONV    <-> FMC_LA08_P    <-> E18 | J25
#    RJ6_SCL     <-> SC6           <-> FMC_LA05_N
#    RJ6_SDO     <-> SD6           <-> FMC_LA05_P
set_property PACKAGE_PIN D21        [get_ports serial_clk_6]
set_property IOSTANDARD LVCMOS18    [get_ports serial_clk_6]
set_property PACKAGE_PIN D20        [get_ports {serial_clk_de[5]}]
set_property IOSTANDARD LVCMOS18    [get_ports {serial_clk_de[5]}]
set_property PACKAGE_PIN C22        [get_ports serial_data_6]
set_property IOSTANDARD LVCMOS18    [get_ports serial_data_6]
set_property PACKAGE_PIN C21        [get_ports {serial_data_de[5]}]
set_property IOSTANDARD LVCMOS18    [get_ports {serial_data_de[5]}]
set_property PACKAGE_PIN J25        [get_ports conv_6]
set_property IOSTANDARD LVCMOS18    [get_ports conv_6]

# RJ7 interface (HPC0 | HPC1)
#    RJ7_CLK     <-> FMC_DP0_M2C_N <-> R1  | AK3
#    RJ7_CLK_DE  <-> FMC_DP0_M2C_P <-> R2  | AK4
#    RJ7_DATA    <-> FMC_LA04_N    <-> L16 | H24
#    RJ7_DATA_DE <-> FMC_LA04_P    <-> L17 | J24
#    RJ7_CONV    <-> FMC_LA03_N    <-> K18 | J22
#    RJ7_SCL     <-> SC0           <-> FMC_LA05_N
#    RJ7_SDO     <-> SD0           <-> FMC_LA05_P
set_property PACKAGE_PIN J22        [get_ports {serial_clk_de[6]}]
set_property IOSTANDARD LVCMOS18    [get_ports {serial_clk_de[6]}]
set_property PACKAGE_PIN J24        [get_ports {serial_data_de[6]}]
set_property IOSTANDARD LVCMOS18    [get_ports {serial_data_de[6]}]

# RJ8 interface (HPC0 | HPC1)
#    RJ8_CLK     <-> FMC_HA01_CC_P <-> -
#    RJ8_CLK_DE  <-> FMC_HA01_CC_N <-> -
#    RJ8_DATA    <-> FMC_HA00_CC_N <-> -
#    RJ8_DATA_DE <-> FMC_HA00_CC_P <-> -
#    RJ8_CONV    <-> FMC_HA05_N    <-> -
#    RJ8_SCL     <-> SC2           <-> FMC_LA05_N
#    RJ8_SDO     <-> SD2           <-> FMC_LA05_P

# I2C interface
#   SDA     <-> FMC_LA05_P  <-> K17 | G25
#   SCL     <-> FMC_LA05_N  <-> J18 | G26
set_property PACKAGE_PIN G25 [get_ports {i2c_sda[0]}]
set_property IOSTANDARD LVCMOS18 [get_ports {i2c_sda[0]}]
set_property PACKAGE_PIN G26 [get_ports {i2c_scl[0]}]
set_property IOSTANDARD LVCMOS18 [get_ports {i2c_scl[0]}]

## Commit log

2021-11-26 add license, readme and gitignore
2021-11-26 add analog-in pcb
2021-11-26 initial commit. Adding analog in hardware, corresponding software and fpga design, draft for fmc hardware, etc.
2021-11-26 fpga-fmc: add LPC pin assignment of FMC connector
2021-11-26 fpga-fmc: fix board layout
2021-11-26 fpga-fmc: add devices from analog-in pcb
2021-11-26 fpga-fmc: add more isolator ics. add i2c switch ic
2021-11-26 fpga-fmc: add 4 channel isolator ic
2021-12-03 analog-in: add comments with PCB mistakes
2021-12-03 sw/arduino: add i2c functions, verify i2c functionality, read saturation check
2021-12-03 sw/arduino: add error compensation
2021-12-10 hw/analog-in: add mistake comment
2021-12-10 hw/fpga-fmc: add and route rs485 transceiver for 3 channels
2021-12-10 sw/arduino/analog-in: work on arduino test sw
2021-12-13 fpga-fmc: add i2c circuit and level shifter for conv signal
2021-12-14 fpga_fmc: route conv signals and more rj channels
2021-12-15 fpga-fmc: route right side
2022-01-06 hw/fpga-fmc: add 5V supply and route remaining CONV signals
2022-02-17 arduino/analog-in: make arduino led blink, improve comments
2022-05-02 hw/fpga-fmc: finalize pcb design and prepare BOM
2022-05-03 hw/fpga-fmc: fix clearance issues
2022-06-01 hw/fpga-fmc: add documentation and code to program fmc eeprom
2022-06-01 hw/fpga-fmc: add cross compile steps
2022-06-07 hdl: create constraints for dino fpga interface. Modify IP for hardware verification
2022-06-07 hw/fpga-fmc: fix connector turned by 180 degrees. add led for 1v8. change i2c package
2022-06-07 sw/arduino/analog-in: work on arduino sw
2022-06-07 hdl: copy all pin assignments to constraint file
    note: RJ8 FMC connection are not connected on the FPGA board, so RJ8 cannot be used with the prototype pcb
2022-08-02 turn FMC connector and reroute signals
2022-08-04 hw/fpga-fmc: rewire pin header and screw terminal.
2022-08-08 hw/fpga-fmc: reposition i2c switch
2022-08-25 hw/fpga-fmc: optimize routing
2022-08-25 sw/arduino/analog-in: improve error output
2022-08-25 hdl/vivado: update constraints to deactivate wrongly routed channels
2022-08-25 hdl/vivado: update block design to deactivate non-working channels
2022-08-26 hw/analog-in: fix mistakes from rev 1
2022-08-26 hw/fmc minor cleanup in layout and schematic
2022-08-26 hw/fpga-fmc: align GND vias
2022-08-29 hw/fpga-fmc: make rs485 termination resistors 0805 for better power rating
2022-09-08 fpga-fmc: last fixes before production of rev B
2022-09-08 hw: add analog-out as copy of analog-in
2022-09-08 ADC board fixes
2022-09-12 hw/analog-out: add part nr for isolator
2022-09-13 hw/fpga-fmc: fix wrong connection on bottom row rj-45 connectors
2022-09-19 hw/fpga-fmc: fix more issues on adapter board
2022-09-19 hdl/vivado: change for rev B PCB
2022-11-03 hdl/vivado: update vivado design
2022-11-03 hw/analog-in: update schematics for analog in
2022-11-03 hw/fpga-fmc/eeprom: add Makefile
2022-11-03 hw/fpga-fmc: make i2c bus id configurable in fmceeprom_write.c
2022-11-03 hw/fpga-fmc/eeprom: use 2to3 to convert fru-generator ot python3
2022-11-03 hw/fpga-fmc/eeprom: install python script to bin/fmc
2022-11-03 hw/fpga-fmc/eeprom: fix makefile installing to wrong path
2022-11-03 First verision of dac schematic
2022-11-03 hw/fpga-fmc/eeprom: fix wrong arg number check
2022-11-18 hdl: add scale and offset and aurora ips to forward dino data to aurora link
2022-11-18 hw/fpga-fmc: update eagle project file
2022-11-18 hdl: add append_seqnum IP and testbench
2022-11-28 hdl: add append seqnum that adds signals to fill up message to a certain size
2022-11-28 hdl: add dinoif_fast_tb that simulates the dino ADC, edge injection logic and delay lines
2022-11-28 hdl: verify and fix dinoif_fast
2022-11-28 hdl: integrate new dinoif_fast into block design
2022-12-12 hdl/vivado: add i2c IP to design
2022-12-12 hw/analog-in: add note
2023-08-14 first revision of dac board
2023-08-14 add polygon
2023-10-13 updated version of board and schematic
2023-10-16 hw: change isolator to si8400ab
2023-10-16 hw: fix part numbers
2023-10-23 hdl: add dac and fix adc IP
2023-10-25 hdl: update board design
2023-12-05 sw/dino-config: add code to configure dino via i2c from SoC
2023-12-05 sw/dino-config: add eeprom reading and writing
2024-04-16 move eagle
2024-04-16 add kicad
2024-04-16 update adc to latest version
2024-04-16 update readme and gitignore
2024-04-16 cleanup
2024-04-18 hdl: fix design to work with LTC2314 ADC
2024-04-26 hw: move eeprom program back to original location
2024-06-18 hdl: make config timer accept new timer value synchronous to separate clock
2024-06-18 hdl: remove GTH LOC constraint
2024-09-25 hdl: add prepend_seqnumg IP
2025-01-24 update vivado files

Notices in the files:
parts and their libraries:
TDN3-1221WISM: COPYRIGHT: Copyright (C) 2018 Accelerated Designs. All rights reserved
LT6654AIS6-2.048: COPYRIGHT: Copyright (C) 2016 Accelerated Designs. All rights reserved
COPYRIGHT: Copyright (C) 2021 Ultra Librarian. All rights reserved.
